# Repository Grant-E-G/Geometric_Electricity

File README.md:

# Geometric Electricity

A passive LC circuit experiment comparing 85-node Euclidean and hyperbolic disks.

The [project outline](notes/one_and_done_hyperbolic_euclidean_board.md) describes the intended board. The [design and measurement plan](notes/research_plan.md) records calculations, equipment, decisions and remaining validation. Open [the KiCad project](hardware/geometric_electricity.kicad_pro) for the current CAD draft; [reproduction commands](code/README.md) generate simulations and verify connectivity.

The hardware is a design draft. Generated manufacturing files remain previews until routing, procurement and assembly checks pass. Bench validation follows assembly.

## Repository Layout

- `notes/`: research plans, reading notes, project logs, and informal planning.
- `math/`: definitions, theorem targets, proof sketches, examples, and open questions.
- `latex/`: manuscript source, macros, bibliography, and TeX inputs.
- `latex/render/`: rendered PDFs and TeX build products. This directory is ignored by git.
- `code/`: one consolidated simulation, CAD-generation and measurement-analysis script.
- `hardware/`: one KiCad project, sparse adjacency/metric data, BOM.
- `build/`: ignored simulation reports, figures, native checks and manufacturing previews.
- `sources/`: source material used during research.
- `sources/pdfs/`: local PDF references. PDF files are ignored by git.

## Working Sequence

1. Read the design/measurement plan and the original outline.
2. Reproduce simulations, probe loading, tolerance and defect sweeps.
3. Generate the KiCad schematic and placement; route and run native checks.
4. Confirm a landed total **below $200**, including PCB/stencil, shipping, tax,
   consumables and spares. Component precision must not break this constraint.
5. Verify the stencil/assembly map, assemble with a measured reflow profile and
   calibrate the RF fixture and probes.
6. Measure low-order responses and pulses, fit overlapping modes where justified,
   and state partial-spectrum limits explicitly.

All generated reports/previews stay in ignored `build/`. With the user-provided
PCBWay shipping-inclusive quote and $10 stencil, the proposed TDK parts give
$170.34 for lead-free HASL or $194.81 for ENIG. These totals retain $15 component
shipping, $20 tax/import and $20 contingency allowances. Component delivery and
any additional stencil shipping remain unconfirmed. The current Abracon BOM
costs $181.48 with HASL; its ENIG scenario exceeds $200. No purchasing or physical
measurements have occurred.

## Coding Guidelines

- Prefer Rust for implementation work. Use Python as a backup, with type checking.
- Prefer functional code when possible. Relax this guideline when it causes performance issues.
- Long functions are fine.
- Avoid inheritance. Object-oriented design is generally discouraged.
- Avoid excessive code fragmentation. Longer files are acceptable when they keep related logic together.
- Lint code aggressively. Use Black for Python formatting.
- Shorter code is almost always better code.

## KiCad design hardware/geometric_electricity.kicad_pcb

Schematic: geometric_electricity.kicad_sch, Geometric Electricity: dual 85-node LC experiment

Parts:
C1, C2, C3, C4, C5, C6, C7, C8, C9, C10, C11, C12, C13, C14, C15, C16, C17, C18, C19, C20, C21, C22, C23, C24, C25, C26, C27, C28, C29, C30, C31, C32, C33, C34, C35, C36, C37, C38, C39, C40, C41, C42, C43, C44, C45, C46, C47, C48, C49, C50, C51, C52, C53, C54, C55, C56, C57, C58, C59, C60, C61, C62, C63, C64, C65, C66, C67, C69, C70, C71, C72, C73, C74, C75, C76, C77, C78, C79, C80, C81, C82, C83, C84, C85, C86, C87, C88, C89, C90, C91, C92, C93, C94, C95, C96, C97, C98, C99, C100, C101, C102, C103, C104, C105, C106, C107, C109, C110, C111, C112, C113, C114, C115, C116, C117, C118, C119, C120, C121, C122, C123, C124, C125, C126, C127, C128, C130, C131, C132, C133, C134, C135, C136, C137, C138, C139, C140, C141, C143, C144, C145, C146, C147, C148, C149, C150, C151, C152, C153, C154, C155, C156, C157, C158, C159, C160, C161, C162, C163, C164, C165, C166, C167, C168, C169, C170, C171, C172, C173, C174, C175, C176, C177, C178, C179, C180, C181, C182, C183, C184, C185, C186, C187, C188, C189, C190, C191, C192, C193, C194, C195, C196, C197, C198, C199, C200, C201, C202, C203, C204, C205, C206, C207, C208, C210, C211, C212, C213, C214, C215, C216, C217, C218, C219, C220, C221, C222, C223, C224, C225, C226, C227, C228, C229, C230, C231, C232, C233, C234, C235, C236, C237, C238, C239, C240, C241, C242, C243, C244, C245, C246, C247, C248, C249, C250, C251, C252, C253, C254, C255, C256, C257, C258, C259, C260, C261, C262, C263, C264, C265, C266, C267, C268, C269, C270, C271, C273, C274, C275, C276, C277, C278, C279, C280, C281, C282, C283, C284, C285, C286, C287, C288, C289, C290, C291, C292, C293, C294, C295, C296, C297, C298, C299, C300, C301, C302, C303, C304, C305, C306, C307, C308, C309, C310, C311, C312, C313, C314, C315, C316, C317, C318, C319, C320, C321, C322, C323, C324, C325, C326, C327, C328, C329, C330, C331, C332, C333, C334, C335, C336, C337, C338, C339, C340, C341, C342, C343, C344, C345, C346, C347, C348, C349, C350, C351, C352, C353, C354, C355, C356, C357, C358, C359, C360, C361, C362, C363, C364, C365, C366, C367, C368, C369, C370, C371, C372, C373, C374, C375, C376, C377, C378, C379, C380, C381, C382, C383, C384, C385, C386, C387, C388, C389, C390, C391, C392, C393, C394, C395, C396, C397, C398, C399, C400, C401, C402, C403, C404, C405, C406, C407, C408, C409, C410, C411, C412, C413, C414, C415, C416, C417, C418, C419, C420, C421, C422, C423, C424, C425, C426, C427, C428, C429, C430, C431, C432, C433, C434, C435, C436, C437, C438, C439, C440, C441, C442, C443, C444, C445, C446, C447, C448, C449, C450, C451, C452, C453, C454, C455, C456, C457, C458, C459, C460, C461, C462, C463, C464, C465, C466, C467, C468, C469, C470, C471, C472, C473, C474, C475, C476, C477, C478, C479, C480, C481, C482, C483, C484, C485, C486, C487, C488, C489, C490, C491, C492, C493, C494, C495, C496, C497, C498, C499, C501, C502, C503, C504, C505, C506, C507, C508, C509, C511, C512, C513, C514, C515, C516, C517, C518, C519, C520, C521, C522, C523, C524, C525, C526, C527, C528, C529, C531, C532, C533, C534, C535, C537, C538, C539, C540, C542, C543, C544, C545, C546, C547, C548, C549, C550, C551, C552, C553, C554, C555, C556, C557, C558, C559, C560, C561, C562, C563, C564, C565, C566, C567, C568, C569, C570, C571, C572, C573, C574, C575, C576, C577, C578, C579, C580, C581, C582, C583, C584, C585, C586, C587, C588, C589, C590, C591, C593, C594, C595, C596, C597, C598, C599, C600, C601, C602, C603, C604, C605, C606, C607, C608, C609, C610, C611, C612, C613, C614, C615, C616, C617, C618, C619, C620, C621, C622, C623, C624, C625, C626, C627, C628, C629, C630, C631, C632, C633, C634, C635, C636, C637, C638, C639, C640, C641, C642, C643, C644, C645, C646, C647, C648, C649, C650, C651, C652, C653, C654, C655, C656, C657, C658, C659, C660, C661, C662, C663, C664, C665, C666, C667, C668, C669, C670, C671, C672, C673, C674, C675, C676, C677, C678, C679, C680, C681, C682, C683, C684, C685, C686, C687, C688, C689, C690, C691, C692, C693, C694, C695, C696, C697, C698, C699: 330p; C_0603_1608Metric
C68, C108, C129, C142, C209, C272, C500, C510, C530, C536, C541, C592: 330p; C_0603_1608Metric; not fitted
J1, J2: SOURCE; PinHeader_1x02_P2.54mm_Vertical
L1, L2, L3, L4, L5, L6, L7, L8, L9, L10, L11, L12, L13, L14, L15, L16, L17, L18, L19, L20, L21, L22, L23, L24, L25, L26, L27, L28, L29, L30, L31, L32, L33, L34, L35, L36, L37, L38, L39, L40, L41, L42, L43, L44, L45, L46, L47, L48, L49, L50, L51, L52, L53, L54, L55, L56, L57, L58, L59, L60, L61, L62, L63, L64, L65, L66, L67, L68, L69, L70, L71, L72, L73, L74, L75, L76, L77, L78, L79, L80, L81, L82, L83, L84, L85, L86, L87, L88, L89, L90, L91, L92, L93, L94, L95, L96, L97, L98, L99, L100, L101, L102, L103, L104, L105, L106, L107, L108, L109, L110, L111, L112, L113, L114, L115, L116, L117, L118, L119, L120, L121, L122, L123, L124, L125, L126, L127, L128, L129, L130, L131, L132, L133, L134, L135, L136, L137, L138, L139, L140, L141, L142, L143, L144, L145, L146, L147, L148, L149, L150, L151, L152, L153, L154, L155, L156, L157, L158, L159, L160, L161, L162, L163, L164, L165, L166, L167, L168, L169, L170: 1u; L_0805_2012Metric
R1, R2: 1k; R_0603_1608Metric
TP1: E00; TestPoint_Pad_D1.0mm
TP2, TP4, TP6, TP8, TP10, TP12, TP14, TP16, TP18, TP20, TP22, TP24, TP26, TP28, TP30, TP32, TP34, TP36, TP38, TP40, TP42, TP44, TP46, TP48, TP50, TP52, TP54, TP56, TP58, TP60, TP62, TP64, TP66, TP68, TP70, TP72, TP74, TP76, TP78, TP80, TP82, TP84, TP86, TP88, TP90, TP92, TP94, TP96, TP98, TP100, TP102, TP104, TP106, TP108, TP110, TP112, TP114, TP116, TP118, TP120, TP122, TP124, TP126, TP128, TP130, TP132, TP134, TP136, TP138, TP140, TP142, TP144, TP146, TP148, TP150, TP152, TP154, TP156, TP158, TP160, TP162, TP164, TP166, TP168, TP170, TP174, TP176, TP178, TP180, TP182, TP184, TP186, TP188, TP190, TP192, TP194, TP196, TP198, TP200, TP202, TP204, TP206, TP208, TP210, TP212, TP214, TP216, TP218, TP220, TP222, TP224, TP226, TP228, TP230, TP232, TP234, TP236, TP238, TP240, TP242, TP244, TP246, TP248, TP250, TP252, TP254, TP256, TP258, TP260, TP262, TP264, TP266, TP268, TP270, TP272, TP274, TP276, TP278, TP280, TP282, TP284, TP286, TP288, TP290, TP292, TP294, TP296, TP298, TP300, TP302, TP304, TP306, TP308, TP310, TP312, TP314, TP316, TP318, TP320, TP322, TP324, TP326, TP328, TP330, TP332, TP334, TP336, TP338, TP340, TP342: GND; TestPoint_Pad_D1.0mm
TP3: E01; TestPoint_Pad_D1.0mm
TP5: E02; TestPoint_Pad_D1.0mm
TP7: E03; TestPoint_Pad_D1.0mm
TP9: E04; TestPoint_Pad_D1.0mm
TP11: E05; TestPoint_Pad_D1.0mm
TP13: E06; TestPoint_Pad_D1.0mm
TP15: E07; TestPoint_Pad_D1.0mm
TP17: E08; TestPoint_Pad_D1.0mm
TP19: E09; TestPoint_Pad_D1.0mm
TP21: E10; TestPoint_Pad_D1.0mm
TP23: E11; TestPoint_Pad_D1.0mm
TP25: E12; TestPoint_Pad_D1.0mm
TP27: E13; TestPoint_Pad_D1.0mm
TP29: E14; TestPoint_Pad_D1.0mm
TP31: E15; TestPoint_Pad_D1.0mm
TP33: E16; TestPoint_Pad_D1.0mm
TP35: E17; TestPoint_Pad_D1.0mm
TP37: E18; TestPoint_Pad_D1.0mm
TP39: E19; TestPoint_Pad_D1.0mm
TP41: E20; TestPoint_Pad_D1.0mm
TP43: E21; TestPoint_Pad_D1.0mm
TP45: E22; TestPoint_Pad_D1.0mm
TP47: E23; TestPoint_Pad_D1.0mm
TP49: E24; TestPoint_Pad_D1.0mm
TP51: E25; TestPoint_Pad_D1.0mm
TP53: E26; TestPoint_Pad_D1.0mm
TP55: E27; TestPoint_Pad_D1.0mm
TP57: E28; TestPoint_Pad_D1.0mm
TP59: E29; TestPoint_Pad_D1.0mm
TP61: E30; TestPoint_Pad_D1.0mm
TP63: E31; TestPoint_Pad_D1.0mm
TP65: E32; TestPoint_Pad_D1.0mm
TP67: E33; TestPoint_Pad_D1.0mm
TP69: E34; TestPoint_Pad_D1.0mm
TP71: E35; TestPoint_Pad_D1.0mm
TP73: E36; TestPoint_Pad_D1.0mm
TP75: E37; TestPoint_Pad_D1.0mm
TP77: E38; TestPoint_Pad_D1.0mm
TP79: E39; TestPoint_Pad_D1.0mm
TP81: E40; TestPoint_Pad_D1.0mm
TP83: E41; TestPoint_Pad_D1.0mm
TP85: E42; TestPoint_Pad_D1.0mm
TP87: E43; TestPoint_Pad_D1.0mm
TP89: E44; TestPoint_Pad_D1.0mm
TP91: E45; TestPoint_Pad_D1.0mm
TP93: E46; TestPoint_Pad_D1.0mm
TP95: E47; TestPoint_Pad_D1.0mm
TP97: E48; TestPoint_Pad_D1.0mm
TP99: E49; TestPoint_Pad_D1.0mm
TP101: E50; TestPoint_Pad_D1.0mm
TP103: E51; TestPoint_Pad_D1.0mm
TP105: E52; TestPoint_Pad_D1.0mm
TP107: E53; TestPoint_Pad_D1.0mm
TP109: E54; TestPoint_Pad_D1.0mm
TP111: E55; TestPoint_Pad_D1.0mm
TP113: E56; TestPoint_Pad_D1.0mm
TP115: E57; TestPoint_Pad_D1.0mm
TP117: E58; TestPoint_Pad_D1.0mm
TP119: E59; TestPoint_Pad_D1.0mm
TP121: E60; TestPoint_Pad_D1.0mm
TP123: E61; TestPoint_Pad_D1.0mm
TP125: E62; TestPoint_Pad_D1.0mm
TP127: E63; TestPoint_Pad_D1.0mm
TP129: E64; TestPoint_Pad_D1.0mm
TP131: E65; TestPoint_Pad_D1.0mm
TP133: E66; TestPoint_Pad_D1.0mm
TP135: E67; TestPoint_Pad_D1.0mm
TP137: E68; TestPoint_Pad_D1.0mm
TP139: E69; TestPoint_Pad_D1.0mm
TP141: E70; TestPoint_Pad_D1.0mm
TP143: E71; TestPoint_Pad_D1.0mm
TP145: E72; TestPoint_Pad_D1.0mm
TP147: E73; TestPoint_Pad_D1.0mm
TP149: E74; TestPoint_Pad_D1.0mm
TP151: E75; TestPoint_Pad_D1.0mm
TP153: E76; TestPoint_Pad_D1.0mm
TP155: E77; TestPoint_Pad_D1.0mm
TP157: E78; TestPoint_Pad_D1.0mm
TP159: E79; TestPoint_Pad_D1.0mm
TP161: E80; TestPoint_Pad_D1.0mm
TP163: E81; TestPoint_Pad_D1.0mm
TP165: E82; TestPoint_Pad_D1.0mm
TP167: E83; TestPoint_Pad_D1.0mm
TP169: E84; TestPoint_Pad_D1.0mm
TP171: E_DRIVE; TestPoint_Pad_D1.0mm
TP172: E_IN; TestPoint_Pad_D1.0mm
TP173: H00; TestPoint_Pad_D1.0mm
TP175: H01; TestPoint_Pad_D1.0mm
TP177: H02; TestPoint_Pad_D1.0mm
TP179: H03; TestPoint_Pad_D1.0mm
TP181: H04; TestPoint_Pad_D1.0mm
TP183: H05; TestPoint_Pad_D1.0mm
TP185: H06; TestPoint_Pad_D1.0mm
TP187: H07; TestPoint_Pad_D1.0mm
TP189: H08; TestPoint_Pad_D1.0mm
TP191: H09; TestPoint_Pad_D1.0mm
TP193: H10; TestPoint_Pad_D1.0mm
TP195: H11; TestPoint_Pad_D1.0mm
TP197: H12; TestPoint_Pad_D1.0mm
TP199: H13; TestPoint_Pad_D1.0mm
TP201: H14; TestPoint_Pad_D1.0mm
TP203: H15; TestPoint_Pad_D1.0mm
TP205: H16; TestPoint_Pad_D1.0mm
TP207: H17; TestPoint_Pad_D1.0mm
TP209: H18; TestPoint_Pad_D1.0mm
TP211: H19; TestPoint_Pad_D1.0mm
TP213: H20; TestPoint_Pad_D1.0mm
TP215: H21; TestPoint_Pad_D1.0mm
TP217: H22; TestPoint_Pad_D1.0mm
TP219: H23; TestPoint_Pad_D1.0mm
TP221: H24; TestPoint_Pad_D1.0mm
TP223: H25; TestPoint_Pad_D1.0mm
TP225: H26; TestPoint_Pad_D1.0mm
TP227: H27; TestPoint_Pad_D1.0mm
TP229: H28; TestPoint_Pad_D1.0mm
TP231: H29; TestPoint_Pad_D1.0mm
TP233: H30; TestPoint_Pad_D1.0mm
TP235: H31; TestPoint_Pad_D1.0mm
TP237: H32; TestPoint_Pad_D1.0mm
TP239: H33; TestPoint_Pad_D1.0mm
TP241: H34; TestPoint_Pad_D1.0mm
TP243: H35; TestPoint_Pad_D1.0mm
TP245: H36; TestPoint_Pad_D1.0mm
TP247: H37; TestPoint_Pad_D1.0mm
TP249: H38; TestPoint_Pad_D1.0mm
TP251: H39; TestPoint_Pad_D1.0mm
TP253: H40; TestPoint_Pad_D1.0mm
TP255: H41; TestPoint_Pad_D1.0mm
TP257: H42; TestPoint_Pad_D1.0mm
TP259: H43; TestPoint_Pad_D1.0mm
TP261: H44; TestPoint_Pad_D1.0mm
TP263: H45; TestPoint_Pad_D1.0mm
TP265: H46; TestPoint_Pad_D1.0mm
TP267: H47; TestPoint_Pad_D1.0mm
TP269: H48; TestPoint_Pad_D1.0mm
TP271: H49; TestPoint_Pad_D1.0mm
TP273: H50; TestPoint_Pad_D1.0mm
TP275: H51; TestPoint_Pad_D1.0mm
TP277: H52; TestPoint_Pad_D1.0mm
TP279: H53; TestPoint_Pad_D1.0mm
TP281: H54; TestPoint_Pad_D1.0mm
TP283: H55; TestPoint_Pad_D1.0mm
TP285: H56; TestPoint_Pad_D1.0mm
TP287: H57; TestPoint_Pad_D1.0mm
TP289: H58; TestPoint_Pad_D1.0mm
TP291: H59; TestPoint_Pad_D1.0mm
TP293: H60; TestPoint_Pad_D1.0mm
TP295: H61; TestPoint_Pad_D1.0mm
TP297: H62; TestPoint_Pad_D1.0mm
TP299: H63; TestPoint_Pad_D1.0mm
TP301: H64; TestPoint_Pad_D1.0mm
TP303: H65; TestPoint_Pad_D1.0mm
TP305: H66; TestPoint_Pad_D1.0mm
TP307: H67; TestPoint_Pad_D1.0mm
TP309: H68; TestPoint_Pad_D1.0mm
TP311: H69; TestPoint_Pad_D1.0mm
TP313: H70; TestPoint_Pad_D1.0mm
TP315: H71; TestPoint_Pad_D1.0mm
TP317: H72; TestPoint_Pad_D1.0mm
TP319: H73; TestPoint_Pad_D1.0mm
TP321: H74; TestPoint_Pad_D1.0mm
TP323: H75; TestPoint_Pad_D1.0mm
TP325: H76; TestPoint_Pad_D1.0mm
TP327: H77; TestPoint_Pad_D1.0mm
TP329: H78; TestPoint_Pad_D1.0mm
TP331: H79; TestPoint_Pad_D1.0mm
TP333: H80; TestPoint_Pad_D1.0mm
TP335: H81; TestPoint_Pad_D1.0mm
TP337: H82; TestPoint_Pad_D1.0mm
TP339: H83; TestPoint_Pad_D1.0mm
TP341: H84; TestPoint_Pad_D1.0mm
TP343: H_DRIVE; TestPoint_Pad_D1.0mm
TP344: H_IN; TestPoint_Pad_D1.0mm

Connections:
E00: C67.1, C68.1, C69.1, C70.1, C71.1, C72.1, C73.1, L1.1, TP1.1
E01: C67.2, C68.2, C74.1, C75.1, C76.1, C77.1, C78.1, L2.1, TP3.1
E02: C69.2, C74.2, C79.1, C80.1, C81.1, C82.1, L3.1, TP5.1
E03: C70.2, C79.2, C83.1, C84.1, C85.1, C86.1, L4.1, TP7.1
E04: C71.2, C83.2, C87.1, C88.1, C89.1, C90.1, L5.1, TP9.1
E05: C72.2, C87.2, C91.1, C92.1, C93.1, C94.1, L6.1, TP11.1
E06: C73.2, C75.2, C91.2, C95.1, C96.1, C97.1, L7.1, TP13.1
E07: C76.2, C95.2, C98.1, C99.1, C100.1, C101.1, L8.1, TP15.1
E08: C77.2, C80.2, C102.1, C103.1, C104.1, C105.1, L9.1, TP17.1
E09: C81.2, C84.2, C106.1, C107.1, C108.1, C109.1, C110.1, L10.1, TP19.1
E10: C85.2, C88.2, C111.1, C112.1, C113.1, C114.1, L11.1, TP21.1
E11: C89.2, C92.2, C115.1, C116.1, C117.1, C118.1, L12.1, TP23.1
E12: C93.2, C96.2, C119.1, C120.1, C121.1, C122.1, L13.1, TP25.1
E13: C78.2, C98.2, C102.2, C123.1, C124.1, C125.1, L14.1, TP27.1
E14: C82.2, C103.2, C106.2, C126.1, C127.1, C128.1, C129.1, L15.1, TP29.1
E15: C86.2, C107.2, C108.2, C111.2, C130.1, C131.1, C132.1, L16.1, TP31.1
E16: C90.2, C112.2, C115.2, C133.1, C134.1, C135.1, L17.1, TP33.1
E17: C94.2, C116.2, C119.2, C136.1, C137.1, C138.1, L18.1, TP35.1
E18: C97.2, C99.2, C120.2, C139.1, C140.1, C141.1, C142.1, L19.1, TP37.1
E19: C100.2, C139.2, C143.1, C144.1, C145.1, C146.1, L20.1, TP39.1
E20: C101.2, C123.2, C143.2, C147.1, C148.1, C149.1, L21.1, TP41.1
E21: C104.2, C124.2, C150.1, C151.1, C152.1, C153.1, L22.1, TP43.1
E22: C105.2, C126.2, C150.2, C154.1, C155.1, C156.1, L23.1, TP45.1
E23: C109.2, C127.2, C157.1, C158.1, C159.1, C160.1, L24.1, TP47.1
E24: C110.2, C130.2, C157.2, C161.1, C162.1, C163.1, L25.1, TP49.1
E25: C113.2, C131.2, C164.1, C165.1, C166.1, C167.1, L26.1, TP51.1
E26: C114.2, C133.2, C164.2, C168.1, C169.1, C170.1, L27.1, TP53.1
E27: C117.2, C134.2, C171.1, C172.1, C173.1, C174.1, L28.1, TP55.1
E28: C118.2, C136.2, C171.2, C175.1, C176.1, C177.1, L29.1, TP57.1
E29: C121.2, C137.2, C178.1, C179.1, C180.1, C181.1, L30.1, TP59.1
E30: C122.2, C140.2, C178.2, C182.1, C183.1, C184.1, L31.1, TP61.1
E31: C125.2, C147.2, C151.2, C185.1, C186.1, C187.1, L32.1, TP63.1
E32: C128.2, C129.2, C154.2, C158.2, C188.1, C189.1, C190.1, L33.1, TP65.1
E33: C132.2, C161.2, C165.2, C191.1, C192.1, C193.1, L34.1, TP67.1
E34: C135.2, C168.2, C172.2, C194.1, C195.1, C196.1, L35.1, TP69.1
E35: C138.2, C175.2, C179.2, C197.1, C198.1, C199.1, L36.1, TP71.1
E36: C141.2, C142.2, C144.2, C182.2, C200.1, C201.1, C202.1, L37.1, TP73.1
E37: C145.2, C148.2, C203.1, C204.1, C205.1, C206.1, L38.1, TP75.1
E38: C152.2, C155.2, C207.1, C208.1, C209.1, C210.1, C211.1, L39.1, TP77.1
E39: C159.2, C162.2, C212.1, C213.1, C214.1, C215.1, L40.1, TP79.1
E40: C166.2, C169.2, C216.1, C217.1, C218.1, C219.1, L41.1, TP81.1
E41: C173.2, C176.2, C220.1, C221.1, C222.1, C223.1, L42.1, TP83.1
E42: C180.2, C183.2, C224.1, C225.1, C226.1, C227.1, L43.1, TP85.1
E43: C146.2, C200.2, C203.2, C228.1, C229.1, C230.1, L44.1, TP87.1
E44: C149.2, C185.2, C204.2, C231.1, C232.1, C233.1, L45.1, TP89.1
E45: C153.2, C186.2, C207.2, C234.1, C235.1, C236.1, L46.1, TP91.1
E46: C156.2, C188.2, C208.2, C209.2, C237.1, C238.1, C239.1, L47.1, TP93.1
E47: C160.2, C189.2, C212.2, C240.1, C241.1, C242.1, L48.1, TP95.1
E48: C163.2, C191.2, C213.2, C243.1, C244.1, C245.1, L49.1, TP97.1
E49: C167.2, C192.2, C216.2, C246.1, C247.1, C248.1, L50.1, TP99.1
E50: C170.2, C194.2, C217.2, C249.1, C250.1, C251.1, L51.1, TP101.1
E51: C174.2, C195.2, C220.2, C252.1, C253.1, C254.1, L52.1, TP103.1
E52: C177.2, C197.2, C221.2, C255.1, C256.1, C257.1, L53.1, TP105.1
E53: C181.2, C198.2, C224.2, C258.1, C259.1, C260.1, L54.1, TP107.1
E54: C184.2, C201.2, C225.2, C261.1, C262.1, C263.1, L55.1, TP109.1
E55: C1.1, C187.2, C231.2, C234.2, C264.1, C265.1, L56.1, TP111.1
E56: C2.1, C190.2, C237.2, C240.2, C266.1, C267.1, L57.1, TP113.1
E57: C3.1, C193.2, C243.2, C246.2, C268.1, C269.1, L58.1, TP115.1
E58: C4.1, C196.2, C249.2, C252.2, C270.1, C271.1, C272.1, L59.1, TP117.1
E59: C5.1, C199.2, C255.2, C258.2, C273.1, C274.1, L60.1, TP119.1
E60: C6.1, C202.2, C228.2, C261.2, C275.1, C276.1, L61.1, TP121.1
E61: C7.1, C8.1, C205.2, C229.2, C277.1, C278.1, L62.1, TP123.1
E62: C9.1, C10.1, C206.2, C232.2, C277.2, C279.1, L63.1, TP125.1
E63: C11.1, C12.1, C210.2, C235.2, C280.1, C281.1, L64.1, TP127.1
E64: C13.1, C14.1, C211.2, C238.2, C280.2, C282.1, L65.1, TP129.1
E65: C15.1, C16.1, C214.2, C241.2, C283.1, C284.1, L66.1, TP131.1
E66: C17.1, C18.1, C215.2, C244.2, C283.2, C285.1, L67.1, TP133.1
E67: C19.1, C20.1, C218.2, C247.2, C286.1, C287.1, L68.1, TP135.1
E68: C21.1, C22.1, C219.2, C250.2, C286.2, C288.1, L69.1, TP137.1
E69: C23.1, C24.1, C222.2, C253.2, C289.1, C290.1, L70.1, TP139.1
E70: C25.1, C26.1, C223.2, C256.2, C289.2, C291.1, L71.1, TP141.1
E71: C27.1, C28.1, C226.2, C259.2, C292.1, C293.1, L72.1, TP143.1
E72: C29.1, C30.1, C227.2, C262.2, C292.2, C294.1, L73.1, TP145.1
E73: C31.1, C32.1, C33.1, C230.2, C275.2, C278.2, L74.1, TP147.1
E74: C34.1, C35.1, C36.1, C233.2, C264.2, C279.2, L75.1, TP149.1
E75: C37.1, C38.1, C39.1, C236.2, C265.2, C281.2, L76.1, TP151.1
E76: C40.1, C41.1, C42.1, C239.2, C266.2, C282.2, L77.1, TP153.1
E77: C43.1, C44.1, C45.1, C242.2, C267.2, C284.2, L78.1, TP155.1
E78: C46.1, C47.1, C48.1, C245.2, C268.2, C285.2, L79.1, TP157.1
E79: C49.1, C50.1, C51.1, C248.2, C269.2, C287.2, L80.1, TP159.1
E80: C52.1, C53.1, C54.1, C251.2, C270.2, C288.2, L81.1, TP161.1
E81: C55.1, C56.1, C57.1, C254.2, C271.2, C272.2, C290.2, L82.1, TP163.1
E82: C58.1, C59.1, C60.1, C257.2, C273.2, C291.2, L83.1, TP165.1
E83: C61.1, C62.1, C63.1, C260.2, C274.2, C293.2, L84.1, TP167.1
E84: C64.1, C65.1, C66.1, C263.2, C276.2, C294.2, L85.1, TP169.1
E_DRIVE: R1.2, TP171.1
E_IN: J1.1, R1.1, TP172.1
GND: C1.2, C2.2, C3.2, C4.2, C5.2, C6.2, C7.2, C8.2, C9.2, C10.2, C11.2, C12.2, C13.2, C14.2, C15.2, C16.2, C17.2, C18.2, C19.2, C20.2, C21.2, C22.2, C23.2, C24.2, C25.2, C26.2, C27.2, C28.2, C29.2, C30.2, C31.2, C32.2, C33.2, C34.2, C35.2, C36.2, C37.2, C38.2, C39.2, C40.2, C41.2, C42.2, C43.2, C44.2, C45.2, C46.2, C47.2, C48.2, C49.2, C50.2, C51.2, C52.2, C53.2, C54.2, C55.2, C56.2, C57.2, C58.2, C59.2, C60.2, C61.2, C62.2, C63.2, C64.2, C65.2, C66.2, C295.2, C296.2, C297.2, C298.2, C299.2, C300.2, C301.2, C302.2, C303.2, C304.2, C305.2, C306.2, C307.2, C308.2, C309.2, C310.2, C311.2, C312.2, C313.2, C314.2, C315.2, C316.2, C317.2, C318.2, C319.2, C320.2, C321.2, C322.2, C323.2, C324.2, C325.2, C326.2, C327.2, C328.2, C329.2, C330.2, C331.2, C332.2, C333.2, C334.2, C335.2, C336.2, C337.2, C338.2, C339.2, C340.2, C341.2, C342.2, C343.2, C344.2, C345.2, C346.2, C347.2, C348.2, C349.2, C350.2, C351.2, C352.2, C353.2, C354.2, C355.2, C356.2, C357.2, C358.2, C359.2, C360.2, C361.2, C362.2, C363.2, C364.2, C365.2, C366.2, C367.2, C368.2, C369.2, C370.2, C371.2, C372.2, C373.2, C374.2, C375.2, C376.2, C377.2, C378.2, C379.2, C380.2, C381.2, C382.2, C383.2, C384.2, C385.2, C386.2, C387.2, C388.2, C389.2, C390.2, C391.2, C392.2, C393.2, C394.2, C395.2, C396.2, C397.2, C398.2, C399.2, C400.2, C401.2, C402.2, C403.2, C404.2, C405.2, C406.2, C407.2, C408.2, C409.2, C410.2, C411.2, C412.2, C413.2, C414.2, C415.2, C416.2, C417.2, C418.2, C419.2, C420.2, C421.2, C422.2, C423.2, C424.2, C425.2, C426.2, C427.2, C428.2, C429.2, C430.2, C431.2, C432.2, C433.2, C434.2, C435.2, C436.2, C437.2, C438.2, C439.2, C440.2, C441.2, C442.2, C443.2, C444.2, C445.2, C446.2, C447.2, C448.2, C449.2, C450.2, C451.2, C452.2, C453.2, C454.2, C455.2, C456.2, C457.2, C458.2, C459.2, C460.2, C461.2, C462.2, C463.2, C464.2, C465.2, C466.2, C467.2, C468.2, C469.2, C470.2, C471.2, C472.2, C473.2, C474.2, C475.2, C476.2, C477.2, C478.2, C479.2, C480.2, C481.2, C482.2, C483.2, C484.2, C485.2, C486.2, C487.2, C488.2, C489.2, C490.2, C491.2, C492.2, C493.2, C494.2, C495.2, C496.2, C497.2, J1.2, J2.2, L1.2, L2.2, L3.2, L4.2, L5.2, L6.2, L7.2, L8.2, L9.2, L10.2, L11.2, L12.2, L13.2, L14.2, L15.2, L16.2, L17.2, L18.2, L19.2, L20.2, L21.2, L22.2, L23.2, L24.2, L25.2, L26.2, L27.2, L28.2, L29.2, L30.2, L31.2, L32.2, L33.2, L34.2, L35.2, L36.2, L37.2, L38.2, L39.2, L40.2, L41.2, L42.2, L43.2, L44.2, L45.2, L46.2, L47.2, L48.2, L49.2, L50.2, L51.2, L52.2, L53.2, L54.2, L55.2, L56.2, L57.2, L58.2, L59.2, L60.2, L61.2, L62.2, L63.2, L64.2, L65.2, L66.2, L67.2, L68.2, L69.2, L70.2, L71.2, L72.2, L73.2, L74.2, L75.2, L76.2, L77.2, L78.2, L79.2, L80.2, L81.2, L82.2, L83.2, L84.2, L85.2, L86.2, L87.2, L88.2, L89.2, L90.2, L91.2, L92.2, L93.2, L94.2, L95.2, L96.2, L97.2, L98.2, L99.2, L100.2, L101.2, L102.2, L103.2, L104.2, L105.2, L106.2, L107.2, L108.2, L109.2, L110.2, L111.2, L112.2, L113.2, L114.2, L115.2, L116.2, L117.2, L118.2, L119.2, L120.2, L121.2, L122.2, L123.2, L124.2, L125.2, L126.2, L127.2, L128.2, L129.2, L130.2, L131.2, L132.2, L133.2, L134.2, L135.2, L136.2, L137.2, L138.2, L139.2, L140.2, L141.2, L142.2, L143.2, L144.2, L145.2, L146.2, L147.2, L148.2, L149.2, L150.2, L151.2, L152.2, L153.2, L154.2, L155.2, L156.2, L157.2, L158.2, L159.2, L160.2, L161.2, L162.2, L163.2, L164.2, L165.2, L166.2, L167.2, L168.2, L169.2, L170.2, TP2.1, TP4.1, TP6.1, TP8.1, TP10.1, TP12.1, TP14.1, TP16.1, TP18.1, TP20.1, TP22.1, TP24.1, TP26.1, TP28.1, TP30.1, TP32.1, TP34.1, TP36.1, TP38.1, TP40.1, TP42.1, TP44.1, TP46.1, TP48.1, TP50.1, TP52.1, TP54.1, TP56.1, TP58.1, TP60.1, TP62.1, TP64.1, TP66.1, TP68.1, TP70.1, TP72.1, TP74.1, TP76.1, TP78.1, TP80.1, TP82.1, TP84.1, TP86.1, TP88.1, TP90.1, TP92.1, TP94.1, TP96.1, TP98.1, TP100.1, TP102.1, TP104.1, TP106.1, TP108.1, TP110.1, TP112.1, TP114.1, TP116.1, TP118.1, TP120.1, TP122.1, TP124.1, TP126.1, TP128.1, TP130.1, TP132.1, TP134.1, TP136.1, TP138.1, TP140.1, TP142.1, TP144.1, TP146.1, TP148.1, TP150.1, TP152.1, TP154.1, TP156.1, TP158.1, TP160.1, TP162.1, TP164.1, TP166.1, TP168.1, TP170.1, TP174.1, TP176.1, TP178.1, TP180.1, TP182.1, TP184.1, TP186.1, TP188.1, TP190.1, TP192.1, TP194.1, TP196.1, TP198.1, TP200.1, TP202.1, TP204.1, TP206.1, TP208.1, TP210.1, TP212.1, TP214.1, TP216.1, TP218.1, TP220.1, TP222.1, TP224.1, TP226.1, TP228.1, TP230.1, TP232.1, TP234.1, TP236.1, TP238.1, TP240.1, TP242.1, TP244.1, TP246.1, TP248.1, TP250.1, TP252.1, TP254.1, TP256.1, TP258.1, TP260.1, TP262.1, TP264.1, TP266.1, TP268.1, TP270.1, TP272.1, TP274.1, TP276.1, TP278.1, TP280.1, TP282.1, TP284.1, TP286.1, TP288.1, TP290.1, TP292.1, TP294.1, TP296.1, TP298.1, TP300.1, TP302.1, TP304.1, TP306.1, TP308.1, TP310.1, TP312.1, TP314.1, TP316.1, TP318.1, TP320.1, TP322.1, TP324.1, TP326.1, TP328.1, TP330.1, TP332.1, TP334.1, TP336.1, TP338.1, TP340.1, TP342.1
H00: C498.1, C499.1, C500.1, C501.1, C502.1, C503.1, C504.1, C505.1, L86.1, TP173.1
H01: C498.2, C506.1, C507.1, C508.1, C509.1, C510.1, C511.1, C512.1, L87.1, TP175.1
H02: C499.2, C500.2, C506.2, C513.1, C514.1, C515.1, C516.1, C517.1, L88.1, TP177.1
H03: C501.2, C513.2, C518.1, C519.1, C520.1, C521.1, C522.1, L89.1, TP179.1
H04: C502.2, C518.2, C523.1, C524.1, C525.1, C526.1, C527.1, L90.1, TP181.1
H05: C503.2, C523.2, C528.1, C529.1, C530.1, C531.1, C532.1, C533.1, L91.1, TP183.1
H06: C504.2, C528.2, C534.1, C535.1, C536.1, C537.1, C538.1, C539.1, L92.1, TP185.1
H07: C505.2, C507.2, C534.2, C540.1, C541.1, C542.1, C543.1, C544.1, L93.1, TP187.1
H08: C508.2, C514.2, C545.1, C546.1, C547.1, C548.1, C549.1, L94.1, TP189.1
H09: C515.2, C519.2, C550.1, C551.1, C552.1, C553.1, C554.1, L95.1, TP191.1
H10: C520.2, C524.2, C555.1, C556.1, C557.1, C558.1, C559.1, L96.1, TP193.1
H11: C525.2, C529.2, C530.2, C560.1, C561.1, C562.1, C563.1, C564.1, L97.1, TP195.1
H12: C531.2, C535.2, C536.2, C565.1, C566.1, C567.1, C568.1, C569.1, L98.1, TP197.1
H13: C537.2, C540.2, C541.2, C570.1, C571.1, C572.1, C573.1, C574.1, L99.1, TP199.1
H14: C509.2, C510.2, C542.2, C575.1, C576.1, C577.1, C578.1, C579.1, L100.1, TP201.1
H15: C511.2, C575.2, C580.1, C581.1, C582.1, C583.1, C584.1, L101.1, TP203.1
H16: C512.2, C545.2, C580.2, C585.1, C586.1, C587.1, C588.1, L102.1, TP205.1
H17: C516.2, C546.2, C589.1, C590.1, C591.1, C592.1, C593.1, C594.1, L103.1, TP207.1
H18: C517.2, C550.2, C589.2, C595.1, C596.1, C597.1, C598.1, L104.1, TP209.1
H19: C521.2, C551.2, C599.1, C600.1, C601.1, C602.1, C603.1, L105.1, TP211.1
H20: C522.2, C555.2, C599.2, C604.1, C605.1, C606.1, C607.1, L106.1, TP213.1
H21: C526.2, C556.2, C608.1, C609.1, C610.1, C611.1, C612.1, L107.1, TP215.1
H22: C527.2, C560.2, C608.2, C613.1, C614.1, C615.1, C616.1, L108.1, TP217.1
H23: C532.2, C561.2, C617.1, C618.1, C619.1, C620.1, C621.1, L109.1, TP219.1
H24: C533.2, C565.2, C617.2, C622.1, C623.1, C624.1, C625.1, L110.1, TP221.1
H25: C538.2, C566.2, C626.1, C627.1, C628.1, C629.1, C630.1, L111.1, TP223.1
H26: C539.2, C570.2, C626.2, C631.1, C632.1, C633.1, C634.1, L112.1, TP225.1
H27: C543.2, C571.2, C635.1, C636.1, C637.1, C638.1, C639.1, L113.1, TP227.1
H28: C544.2, C576.2, C635.2, C640.1, C641.1, C642.1, C643.1, L114.1, TP229.1
H29: C295.1, C296.1, C297.1, C577.2, C581.2, C644.1, C645.1, L115.1, TP231.1
H30: C298.1, C299.1, C300.1, C547.2, C585.2, C646.1, C647.1, L116.1, TP233.1
H31: C301.1, C302.1, C303.1, C548.2, C590.2, C648.1, C649.1, L117.1, TP235.1
H32: C304.1, C305.1, C306.1, C552.2, C595.2, C650.1, C651.1, L118.1, TP237.1
H33: C307.1, C308.1, C309.1, C553.2, C600.2, C652.1, C653.1, L119.1, TP239.1
H34: C310.1, C311.1, C312.1, C557.2, C604.2, C654.1, C655.1, L120.1, TP241.1
H35: C313.1, C314.1, C315.1, C558.2, C609.2, C656.1, C657.1, L121.1, TP243.1
H36: C316.1, C317.1, C318.1, C562.2, C613.2, C658.1, C659.1, L122.1, TP245.1
H37: C319.1, C320.1, C321.1, C563.2, C618.2, C660.1, C661.1, L123.1, TP247.1
H38: C322.1, C323.1, C324.1, C567.2, C622.2, C662.1, C663.1, L124.1, TP249.1
H39: C325.1, C326.1, C327.1, C568.2, C627.2, C664.1, C665.1, L125.1, TP251.1
H40: C328.1, C329.1, C330.1, C572.2, C631.2, C666.1, C667.1, L126.1, TP253.1
H41: C331.1, C332.1, C333.1, C573.2, C636.2, C668.1, C669.1, L127.1, TP255.1
H42: C334.1, C335.1, C336.1, C578.2, C640.2, C670.1, C671.1, L128.1, TP257.1
H43: C337.1, C338.1, C339.1, C582.2, C586.2, C672.1, C673.1, L129.1, TP259.1
H44: C340.1, C341.1, C342.1, C343.1, C549.2, C646.2, C648.2, L130.1, TP261.1
H45: C344.1, C345.1, C346.1, C591.2, C592.2, C596.2, C674.1, C675.1, L131.1, TP263.1
H46: C347.1, C348.1, C349.1, C350.1, C554.2, C650.2, C652.2, L132.1, TP265.1
H47: C351.1, C352.1, C353.1, C601.2, C605.2, C676.1, C677.1, L133.1, TP267.1
H48: C354.1, C355.1, C356.1, C357.1, C559.2, C654.2, C656.2, L134.1, TP269.1
H49: C358.1, C359.1, C360.1, C610.2, C614.2, C678.1, C679.1, L135.1, TP271.1
H50: C361.1, C362.1, C363.1, C364.1, C564.2, C658.2, C660.2, L136.1, TP273.1
H51: C365.1, C366.1, C367.1, C619.2, C623.2, C680.1, C681.1, L137.1, TP275.1
H52: C368.1, C369.1, C370.1, C371.1, C569.2, C662.2, C664.2, L138.1, TP277.1
H53: C372.1, C373.1, C374.1, C628.2, C632.2, C682.1, C683.1, L139.1, TP279.1
H54: C375.1, C376.1, C377.1, C378.1, C574.2, C666.2, C668.2, L140.1, TP281.1
H55: C379.1, C380.1, C381.1, C637.2, C641.2, C684.1, C685.1, L141.1, TP283.1
H56: C382.1, C383.1, C384.1, C385.1, C579.2, C644.2, C670.2, L142.1, TP285.1
H57: C386.1, C387.1, C388.1, C389.1, C583.2, C645.2, C686.1, L143.1, TP287.1
H58: C390.1, C391.1, C392.1, C393.1, C587.2, C647.2, C687.1, L144.1, TP289.1
H59: C394.1, C395.1, C396.1, C397.1, C593.2, C649.2, C688.1, L145.1, TP291.1
H60: C398.1, C399.1, C400.1, C401.1, C597.2, C651.2, C689.1, L146.1, TP293.1
H61: C402.1, C403.1, C404.1, C405.1, C602.2, C653.2, C690.1, L147.1, TP295.1
H62: C406.1, C407.1, C408.1, C409.1, C606.2, C655.2, C691.1, L148.1, TP297.1
H63: C410.1, C411.1, C412.1, C413.1, C611.2, C657.2, C692.1, L149.1, TP299.1
H64: C414.1, C415.1, C416.1, C417.1, C615.2, C659.2, C693.1, L150.1, TP301.1
H65: C418.1, C419.1, C420.1, C421.1, C620.2, C661.2, C694.1, L151.1, TP303.1
H66: C422.1, C423.1, C424.1, C425.1, C624.2, C663.2, C695.1, L152.1, TP305.1
H67: C426.1, C427.1, C428.1, C429.1, C629.2, C665.2, C696.1, L153.1, TP307.1
H68: C430.1, C431.1, C432.1, C433.1, C633.2, C667.2, C697.1, L154.1, TP309.1
H69: C434.1, C435.1, C436.1, C437.1, C638.2, C669.2, C698.1, L155.1, TP311.1
H70: C438.1, C439.1, C440.1, C441.1, C642.2, C671.2, C699.1, L156.1, TP313.1
H71: C442.1, C443.1, C444.1, C445.1, C584.2, C672.2, C686.2, L157.1, TP315.1
H72: C446.1, C447.1, C448.1, C449.1, C588.2, C673.2, C687.2, L158.1, TP317.1
H73: C450.1, C451.1, C452.1, C453.1, C594.2, C674.2, C688.2, L159.1, TP319.1
H74: C454.1, C455.1, C456.1, C457.1, C598.2, C675.2, C689.2, L160.1, TP321.1
H75: C458.1, C459.1, C460.1, C461.1, C603.2, C676.2, C690.2, L161.1, TP323.1
H76: C462.1, C463.1, C464.1, C465.1, C607.2, C677.2, C691.2, L162.1, TP325.1
H77: C466.1, C467.1, C468.1, C469.1, C612.2, C678.2, C692.2, L163.1, TP327.1
H78: C470.1, C471.1, C472.1, C473.1, C616.2, C679.2, C693.2, L164.1, TP329.1
H79: C474.1, C475.1, C476.1, C477.1, C621.2, C680.2, C694.2, L165.1, TP331.1
H80: C478.1, C479.1, C480.1, C481.1, C625.2, C681.2, C695.2, L166.1, TP333.1
H81: C482.1, C483.1, C484.1, C485.1, C630.2, C682.2, C696.2, L167.1, TP335.1
H82: C486.1, C487.1, C488.1, C489.1, C634.2, C683.2, C697.2, L168.1, TP337.1
H83: C490.1, C491.1, C492.1, C493.1, C639.2, C684.2, C698.2, L169.1, TP339.1
H84: C494.1, C495.1, C496.1, C497.1, C643.2, C685.2, C699.2, L170.1, TP341.1
H_DRIVE: R2.2, TP343.1
H_IN: J2.1, R2.1, TP344.1

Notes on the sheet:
DRAFT: 1uH / 330pF; AIML-0805-1R0K-T; Q>=45 at 10MHz; use 10x probes. All node labels are global within this sheet.

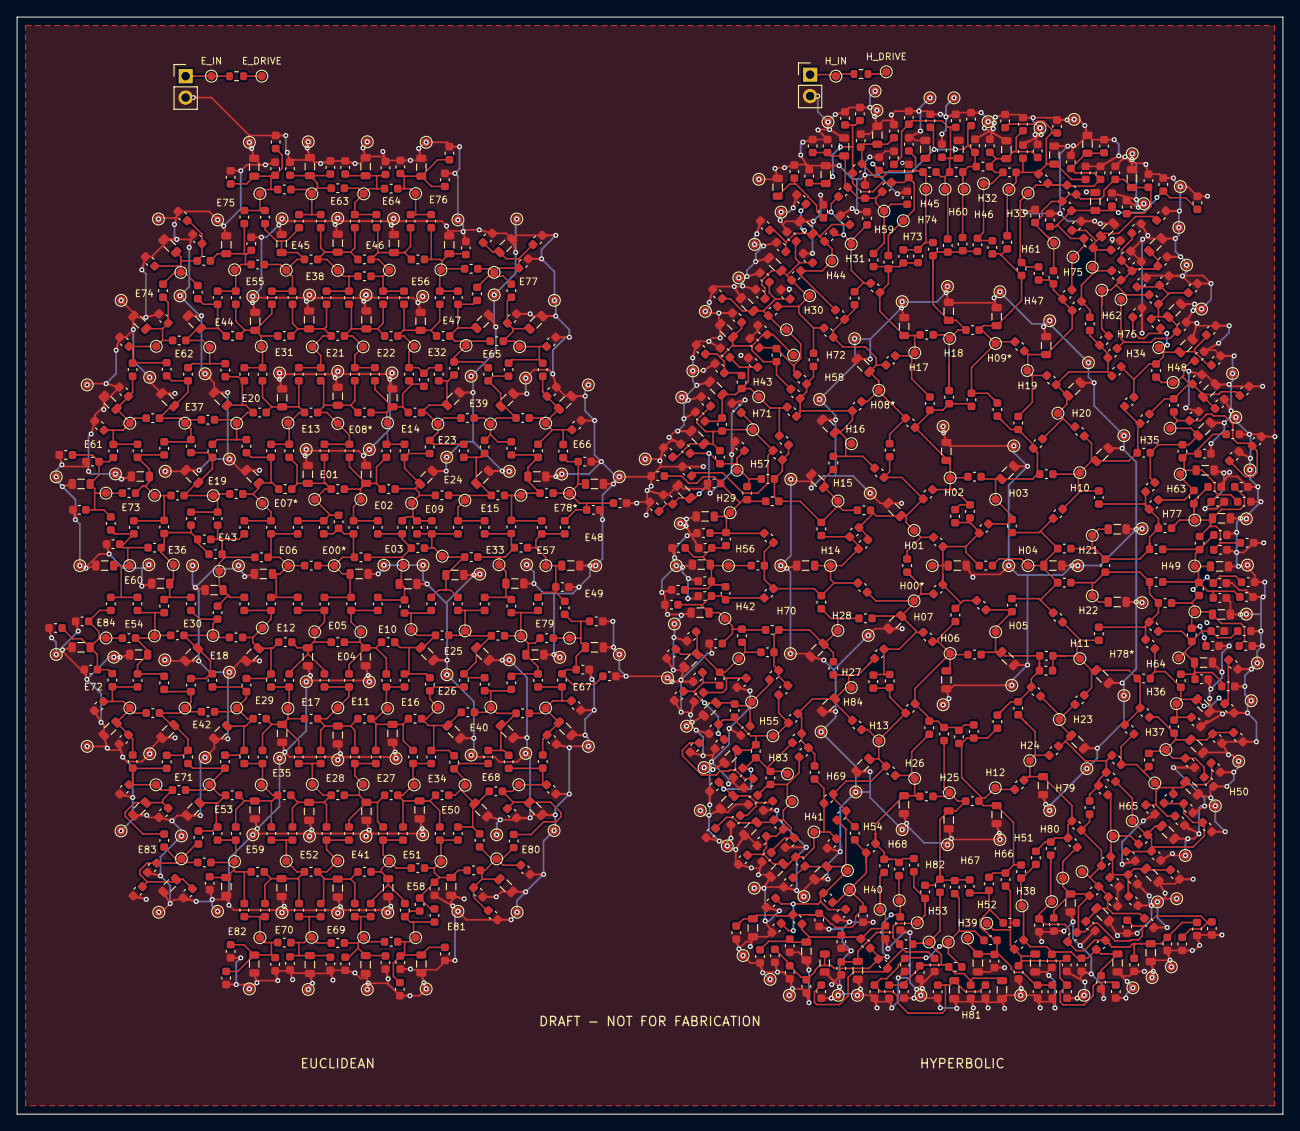
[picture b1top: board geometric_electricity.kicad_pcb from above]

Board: 2 copper layers, 150.0 x 130.0 mm, 1217 parts (0 on the bottom side), 175 nets.

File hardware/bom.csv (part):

Reference,Value,Footprint,DNP,Role,MPN
L1,1u,Inductor_SMD:L_0805_2012Metric,False,E00 inductor; Abracon AIML-0805-1R0K-T 10% Q>=45 at 10MHz,AIML-0805-1R0K-T
L2,1u,Inductor_SMD:L_0805_2012Metric,False,E01 inductor; Abracon AIML-0805-1R0K-T 10% Q>=45 at 10MHz,AIML-0805-1R0K-T
L3,1u,Inductor_SMD:L_0805_2012Metric,False,E02 inductor; Abracon AIML-0805-1R0K-T 10% Q>=45 at 10MHz,AIML-0805-1R0K-T
L4,1u,Inductor_SMD:L_0805_2012Metric,False,E03 inductor; Abracon AIML-0805-1R0K-T 10% Q>=45 at 10MHz,AIML-0805-1R0K-T
L5,1u,Inductor_SMD:L_0805_2012Metric,False,E04 inductor; Abracon AIML-0805-1R0K-T 10% Q>=45 at 10MHz,AIML-0805-1R0K-T
L6,1u,Inductor_SMD:L_0805_2012Metric,False,E05 inductor; Abracon AIML-0805-1R0K-T 10% Q>=45 at 10MHz,AIML-0805-1R0K-T
L7,1u,Inductor_SMD:L_0805_2012Metric,False,E06 inductor; Abracon AIML-0805-1R0K-T 10% Q>=45 at 10MHz,AIML-0805-1R0K-T
L8,1u,Inductor_SMD:L_0805_2012Metric,False,E07 inductor; Abracon AIML-0805-1R0K-T 10% Q>=45 at 10MHz,AIML-0805-1R0K-T
L9,1u,Inductor_SMD:L_0805_2012Metric,False,E08 inductor; Abracon AIML-0805-1R0K-T 10% Q>=45 at 10MHz,AIML-0805-1R0K-T
L10,1u,Inductor_SMD:L_0805_2012Metric,False,E09 inductor; Abracon AIML-0805-1R0K-T 10% Q>=45 at 10MHz,AIML-0805-1R0K-T
L11,1u,Inductor_SMD:L_0805_2012Metric,False,E10 inductor; Abracon AIML-0805-1R0K-T 10% Q>=45 at 10MHz,AIML-0805-1R0K-T
L12,1u,Inductor_SMD:L_0805_2012Metric,False,E11 inductor; Abracon AIML-0805-1R0K-T 10% Q>=45 at 10MHz,AIML-0805-1R0K-T
L13,1u,Inductor_SMD:L_0805_2012Metric,False,E12 inductor; Abracon AIML-0805-1R0K-T 10% Q>=45 at 10MHz,AIML-0805-1R0K-T
L14,1u,Inductor_SMD:L_0805_2012Metric,False,E13 inductor; Abracon AIML-0805-1R0K-T 10% Q>=45 at 10MHz,AIML-0805-1R0K-T
L15,1u,Inductor_SMD:L_0805_2012Metric,False,E14 inductor; Abracon AIML-0805-1R0K-T 10% Q>=45 at 10MHz,AIML-0805-1R0K-T
L16,1u,Inductor_SMD:L_0805_2012Metric,False,E15 inductor; Abracon AIML-0805-1R0K-T 10% Q>=45 at 10MHz,AIML-0805-1R0K-T
L17,1u,Inductor_SMD:L_0805_2012Metric,False,E16 inductor; Abracon AIML-0805-1R0K-T 10% Q>=45 at 10MHz,AIML-0805-1R0K-T
L18,1u,Inductor_SMD:L_0805_2012Metric,False,E17 inductor; Abracon AIML-0805-1R0K-T 10% Q>=45 at 10MHz,AIML-0805-1R0K-T
L19,1u,Inductor_SMD:L_0805_2012Metric,False,E18 inductor; Abracon AIML-0805-1R0K-T 10% Q>=45 at 10MHz,AIML-0805-1R0K-T
L20,1u,Inductor_SMD:L_0805_2012Metric,False,E19 inductor; Abracon AIML-0805-1R0K-T 10% Q>=45 at 10MHz,AIML-0805-1R0K-T
L21,1u,Inductor_SMD:L_0805_2012Metric,False,E20 inductor; Abracon AIML-0805-1R0K-T 10% Q>=45 at 10MHz,AIML-0805-1R0K-T
L22,1u,Inductor_SMD:L_0805_2012Metric,False,E21 inductor; Abracon AIML-0805-1R0K-T 10% Q>=45 at 10MHz,AIML-0805-1R0K-T
L23,1u,Inductor_SMD:L_0805_2012Metric,False,E22 inductor; Abracon AIML-0805-1R0K-T 10% Q>=45 at 10MHz,AIML-0805-1R0K-T
L24,1u,Inductor_SMD:L_0805_2012Metric,False,E23 inductor; Abracon AIML-0805-1R0K-T 10% Q>=45 at 10MHz,AIML-0805-1R0K-T
L25,1u,Inductor_SMD:L_0805_2012Metric,False,E24 inductor; Abracon AIML-0805-1R0K-T 10% Q>=45 at 10MHz,AIML-0805-1R0K-T
L26,1u,Inductor_SMD:L_0805_2012Metric,False,E25 inductor; Abracon AIML-0805-1R0K-T 10% Q>=45 at 10MHz,AIML-0805-1R0K-T
L27,1u,Inductor_SMD:L_0805_2012Metric,False,E26 inductor; Abracon AIML-0805-1R0K-T 10% Q>=45 at 10MHz,AIML-0805-1R0K-T
L28,1u,Inductor_SMD:L_0805_2012Metric,False,E27 inductor; Abracon AIML-0805-1R0K-T 10% Q>=45 at 10MHz,AIML-0805-1R0K-T
L29,1u,Inductor_SMD:L_0805_2012Metric,False,E28 inductor; Abracon AIML-0805-1R0K-T 10% Q>=45 at 10MHz,AIML-0805-1R0K-T
L30,1u,Inductor_SMD:L_0805_2012Metric,False,E29 inductor; Abracon AIML-0805-1R0K-T 10% Q>=45 at 10MHz,AIML-0805-1R0K-T
L31,1u,Inductor_SMD:L_0805_2012Metric,False,E30 inductor; Abracon AIML-0805-1R0K-T 10% Q>=45 at 10MHz,AIML-0805-1R0K-T
L32,1u,Inductor_SMD:L_0805_2012Metric,False,E31 inductor; Abracon AIML-0805-1R0K-T 10% Q>=45 at 10MHz,AIML-0805-1R0K-T
L33,1u,Inductor_SMD:L_0805_2012Metric,False,E32 inductor; Abracon AIML-0805-1R0K-T 10% Q>=45 at 10MHz,AIML-0805-1R0K-T
L34,1u,Inductor_SMD:L_0805_2012Metric,False,E33 inductor; Abracon AIML-0805-1R0K-T 10% Q>=45 at 10MHz,AIML-0805-1R0K-T
L35,1u,Inductor_SMD:L_0805_2012Metric,False,E34 inductor; Abracon AIML-0805-1R0K-T 10% Q>=45 at 10MHz,AIML-0805-1R0K-T
L36,1u,Inductor_SMD:L_0805_2012Metric,False,E35 inductor; Abracon AIML-0805-1R0K-T 10% Q>=45 at 10MHz,AIML-0805-1R0K-T
L37,1u,Inductor_SMD:L_0805_2012Metric,False,E36 inductor; Abracon AIML-0805-1R0K-T 10% Q>=45 at 10MHz,AIML-0805-1R0K-T
L38,1u,Inductor_SMD:L_0805_2012Metric,False,E37 inductor; Abracon AIML-0805-1R0K-T 10% Q>=45 at 10MHz,AIML-0805-1R0K-T
L39,1u,Inductor_SMD:L_0805_2012Metric,False,E38 inductor; Abracon AIML-0805-1R0K-T 10% Q>=45 at 10MHz,AIML-0805-1R0K-T
L40,1u,Inductor_SMD:L_0805_2012Metric,False,E39 inductor; Abracon AIML-0805-1R0K-T 10% Q>=45 at 10MHz,AIML-0805-1R0K-T
L41,1u,Inductor_SMD:L_0805_2012Metric,False,E40 inductor; Abracon AIML-0805-1R0K-T 10% Q>=45 at 10MHz,AIML-0805-1R0K-T
L42,1u,Inductor_SMD:L_0805_2012Metric,False,E41 inductor; Abracon AIML-0805-1R0K-T 10% Q>=45 at 10MHz,AIML-0805-1R0K-T
L43,1u,Inductor_SMD:L_0805_2012Metric,False,E42 inductor; Abracon AIML-0805-1R0K-T 10% Q>=45 at 10MHz,AIML-0805-1R0K-T
L44,1u,Inductor_SMD:L_0805_2012Metric,False,E43 inductor; Abracon AIML-0805-1R0K-T 10% Q>=45 at 10MHz,AIML-0805-1R0K-T
L45,1u,Inductor_SMD:L_0805_2012Metric,False,E44 inductor; Abracon AIML-0805-1R0K-T 10% Q>=45 at 10MHz,AIML-0805-1R0K-T
L46,1u,Inductor_SMD:L_0805_2012Metric,False,E45 inductor; Abracon AIML-0805-1R0K-T 10% Q>=45 at 10MHz,AIML-0805-1R0K-T
L47,1u,Inductor_SMD:L_0805_2012Metric,False,E46 inductor; Abracon AIML-0805-1R0K-T 10% Q>=45 at 10MHz,AIML-0805-1R0K-T
L48,1u,Inductor_SMD:L_0805_2012Metric,False,E47 inductor; Abracon AIML-0805-1R0K-T 10% Q>=45 at 10MHz,AIML-0805-1R0K-T
L49,1u,Inductor_SMD:L_0805_2012Metric,False,E48 inductor; Abracon AIML-0805-1R0K-T 10% Q>=45 at 10MHz,AIML-0805-1R0K-T
L50,1u,Inductor_SMD:L_0805_2012Metric,False,E49 inductor; Abracon AIML-0805-1R0K-T 10% Q>=45 at 10MHz,AIML-0805-1R0K-T
L51,1u,Inductor_SMD:L_0805_2012Metric,False,E50 inductor; Abracon AIML-0805-1R0K-T 10% Q>=45 at 10MHz,AIML-0805-1R0K-T
L52,1u,Inductor_SMD:L_0805_2012Metric,False,E51 inductor; Abracon AIML-0805-1R0K-T 10% Q>=45 at 10MHz,AIML-0805-1R0K-T
L53,1u,Inductor_SMD:L_0805_2012Metric,False,E52 inductor; Abracon AIML-0805-1R0K-T 10% Q>=45 at 10MHz,AIML-0805-1R0K-T
L54,1u,Inductor_SMD:L_0805_2012Metric,False,E53 inductor; Abracon AIML-0805-1R0K-T 10% Q>=45 at 10MHz,AIML-0805-1R0K-T
L55,1u,Inductor_SMD:L_0805_2012Metric,False,E54 inductor; Abracon AIML-0805-1R0K-T 10% Q>=45 at 10MHz,AIML-0805-1R0K-T
L56,1u,Inductor_SMD:L_0805_2012Metric,False,E55 inductor; Abracon AIML-0805-1R0K-T 10% Q>=45 at 10MHz,AIML-0805-1R0K-T
C1,330p,Capacitor_SMD:C_0603_1608Metric,False,E55 boundary coupling 1/1,CC0603JRNPO9BN331
L57,1u,Inductor_SMD:L_0805_2012Metric,False,E56 inductor; Abracon AIML-0805-1R0K-T 10% Q>=45 at 10MHz,AIML-0805-1R0K-T
C2,330p,Capacitor_SMD:C_0603_1608Metric,False,E56 boundary coupling 1/1,CC0603JRNPO9BN331
L58,1u,Inductor_SMD:L_0805_2012Metric,False,E57 inductor; Abracon AIML-0805-1R0K-T 10% Q>=45 at 10MHz,AIML-0805-1R0K-T
C3,330p,Capacitor_SMD:C_0603_1608Metric,False,E57 boundary coupling 1/1,CC0603JRNPO9BN331
L59,1u,Inductor_SMD:L_0805_2012Metric,False,E58 inductor; Abracon AIML-0805-1R0K-T 10% Q>=45 at 10MHz,AIML-0805-1R0K-T
C4,330p,Capacitor_SMD:C_0603_1608Metric,False,E58 boundary coupling 1/1,CC0603JRNPO9BN331
L60,1u,Inductor_SMD:L_0805_2012Metric,False,E59 inductor; Abracon AIML-0805-1R0K-T 10% Q>=45 at 10MHz,AIML-0805-1R0K-T
C5,330p,Capacitor_SMD:C_0603_1608Metric,False,E59 boundary coupling 1/1,CC0603JRNPO9BN331
L61,1u,Inductor_SMD:L_0805_2012Metric,False,E60 inductor; Abracon AIML-0805-1R0K-T 10% Q>=45 at 10MHz,AIML-0805-1R0K-T
C6,330p,Capacitor_SMD:C_0603_1608Metric,False,E60 boundary coupling 1/1,CC0603JRNPO9BN331
L62,1u,Inductor_SMD:L_0805_2012Metric,False,E61 inductor; Abracon AIML-0805-1R0K-T 10% Q>=45 at 10MHz,AIML-0805-1R0K-T
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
